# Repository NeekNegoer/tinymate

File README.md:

# TinyMate ♟️

**Eight Pin Gambit** — a smart chessboard that sees your pieces, powered by a single 8-pin ATtiny412.

> 🇧🇷 Um tabuleiro de xadrez inteligente que detecta as peças e joga online pelo Lichess, controlado por um microcontrolador de apenas 8 pinos.

Built for the [Hack Club 8-Pin Grant](https://8-pin-grant.hackclub.com/).

## How it works

```
[Phone/PC] ⇄ UART ⇄ [ATtiny412] ⇄ I2C ⇄ [MCP23017] ⇄ [8×8 reed switch matrix]
```

- Every piece has a small magnet in its base; every square has a reed switch (+ a 1N4148 diode to prevent ghosting).
- The ATtiny412 scans the 8×8 matrix through an MCP23017 I/O expander (8 rows out, 8 columns in) and reports occupied squares over UART.
- Software on the phone/PC compares board states to infer moves (from the starting position, including captures, castling and promotion) and plays them through the [Lichess Board API](https://lichess.org/api#tag/Board).

## ATtiny412 pinout

| Pin | Name | Use |
|---|---|---|
| 1 | VDD | 5 V |
| 2 | PA6 | UART TX |
| 3 | PA7 | UART RX |
| 4 | PA1 | I2C SDA |
| 5 | PA2 | I2C SCL |
| 6 | PA0 | UPDI (programming) |
| 7 | PA3 | Status LED |
| 8 | GND | Ground |

## Controller board parts (draft)

| Ref | Part | Notes |
|---|---|---|
| U1 | ATtiny412 (SOIC-8) | the brain |
| U2 | MCP23017 (SOIC-28) | A0–A2 → GND (addr 0x20), RESET → VCC |
| R1, R2 | 4.7 kΩ | I2C pull-ups |
| R3 + LED1 | 1 kΩ + LED | status |
| R4 | 10 kΩ | MCP23017 RESET pull-up |
| C1, C2 | 100 nF | decoupling, one per IC |
| C3 | 10 µF | bulk |
| J1 | 1×4 header | 5V / GND / TX / RX (also powers the board) |
| J2 | 1×3 header | UPDI: 5V / UPDI / GND |
| J3 | 2×8 header | matrix rows + columns |

## Status

- [x] Architecture, pinout and parts list
- [ ] Schematic (KiCad)
- [ ] PCB layout (KiCad, 2 layers)
- [ ] BOM with part numbers + cost check
- [ ] Submit to 8-Pin Grant
- [ ] Assemble, firmware, demo video
- [ ] Lichess bridge app

Progress log: [journal.md](journal.md)

## Author

Pietro Justino — [@NeekNegoer](https://github.com/NeekNegoer)

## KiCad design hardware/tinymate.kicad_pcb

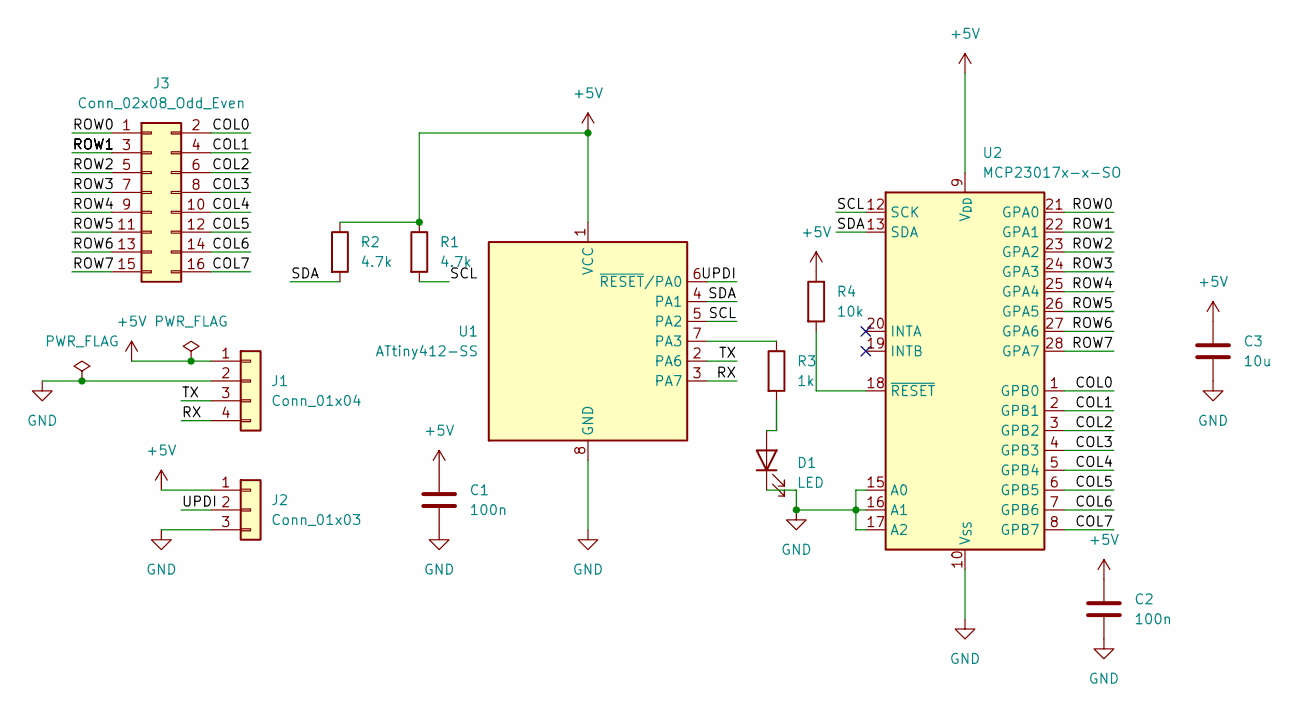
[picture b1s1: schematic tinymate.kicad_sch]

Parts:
C1, C2: 100n; C_0805_2012Metric_Pad1.18x1.45mm_HandSolder; MPN CL21B104KBCNNNC
C3: 10u; C_0805_2012Metric_Pad1.18x1.45mm_HandSolder; MPN CL21B106KOQNNNE
D1: LED; LED_0805_2012Metric_Pad1.15x1.40mm_HandSolder; MPN LTST-C171KRKT
J1: Conn_01x04; PinHeader_1x04_P2.54mm_Vertical; MPN PRPC040SAAN-RC
J2: Conn_01x03; PinHeader_1x03_P2.54mm_Vertical; MPN PRPC040SAAN-RC
J3: Conn_02x08_Odd_Even; PinHeader_2x08_P2.54mm_Vertical; MPN PRPC040SAAN-RC
R1, R2: 4.7k; R_0805_2012Metric_Pad1.20x1.40mm_HandSolder; MPN RC0805FR-074K7L
R3: 1k; R_0805_2012Metric_Pad1.20x1.40mm_HandSolder; MPN RC0805FR-071KL
R4: 10k; R_0805_2012Metric_Pad1.20x1.40mm_HandSolder; MPN RC0805FR-0710KL
U1: ATtiny412-SS; SOIC-8_3.9x4.9mm_P1.27mm; MPN ATTINY412-SSN
U2: MCP23017x-x-SO; SOIC-28W_7.5x17.9mm_P1.27mm; MPN MCP23017-E/SO

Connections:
+5V: C1.1, C2.1, C3.1, J1.1, J2.1, R1.1, R2.1, R4.1, U1.1 (VCC), U2.9 (V_{DD})
/COL0: J3.2, U2.1 (GPB0)
/COL1: J3.4, U2.2 (GPB1)
/COL2: J3.6, U2.3 (GPB2)
/COL3: J3.8, U2.4 (GPB3)
/COL4: J3.10, U2.5 (GPB4)
/COL5: J3.12, U2.6 (GPB5)
/COL6: J3.14, U2.7 (GPB6)
/COL7: J3.16, U2.8 (GPB7)
/ROW0: J3.1, U2.21 (GPA0)
/ROW1: J3.3, U2.22 (GPA1)
/ROW2: J3.5, U2.23 (GPA2)
/ROW3: J3.7, U2.24 (GPA3)
/ROW4: J3.9, U2.25 (GPA4)
/ROW5: J3.11, U2.26 (GPA5)
/ROW6: J3.13, U2.27 (GPA6)
/ROW7: J3.15, U2.28 (GPA7)
/RX: J1.4, U1.3 (PA7)
/SCL: R1.2, U1.5 (PA2), U2.12 (SCK)
/SDA: R2.2, U1.4 (PA1), U2.13 (SDA)
/TX: J1.3, U1.2 (PA6)
/UPDI: J2.2, U1.6 (~RESET/PA0)
GND: C1.2, C2.2, C3.2, D1.1 (K), J1.2, J2.3, U1.8 (GND), U2.10 (V_{SS}), U2.15 (A0), U2.16 (A1), U2.17 (A2)
unnamed: D1.2 (A), R3.2
unnamed: R3.1, U1.7 (PA3)
unnamed: R4.2, U2.18 (~RESET)

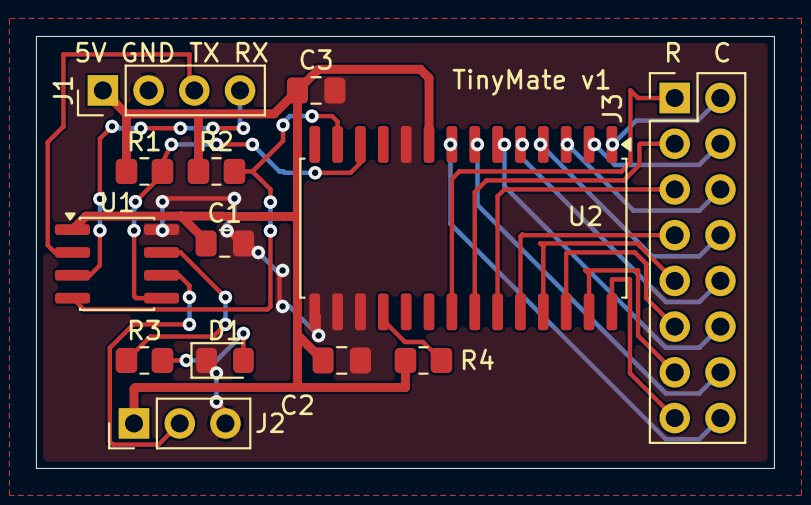
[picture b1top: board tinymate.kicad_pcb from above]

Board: 2 copper layers, 41.0 x 24.0 mm, 13 parts (0 on the bottom side), 26 nets.

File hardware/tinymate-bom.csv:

Reference,Qty on board,Value,Footprint,Manufacturer,Part Number,DigiKey Part Number,Order Qty,Unit Price (USD),Extended Price (USD)
U1,1,ATtiny412-SS,Package_SO:SOIC-8_3.9x4.9mm_P1.27mm,Microchip Technology,ATTINY412-SSN,ATTINY412-SSN-ND,2,0.56,1.12
U2,1,MCP23017,Package_SO:SOIC-28W_7.5x17.9mm_P1.27mm,Microchip Technology,MCP23017-E/SO,MCP23017-E/SO-ND,1,1.62,1.62
"R1,R2",2,4.7k,Resistor_SMD:R_0805_2012Metric_Pad1.20x1.40mm_HandSolder,YAGEO,RC0805FR-074K7L,311-4.70KCRCT-ND,10,0.038,0.38
R3,1,1k,Resistor_SMD:R_0805_2012Metric_Pad1.20x1.40mm_HandSolder,YAGEO,RC0805FR-071KL,311-1.00KCRCT-ND,10,0.038,0.38
R4,1,10k,Resistor_SMD:R_0805_2012Metric_Pad1.20x1.40mm_HandSolder,YAGEO,RC0805FR-0710KL,311-10.0KCRCT-ND,10,0.038,0.38
"C1,C2",2,100n,Capacitor_SMD:C_0805_2012Metric_Pad1.18x1.45mm_HandSolder,Samsung Electro-Mechanics,CL21B104KBCNNNC,1276-1003-1-ND,10,0.045,0.45
C3,1,10u,Capacitor_SMD:C_0805_2012Metric_Pad1.18x1.45mm_HandSolder,Samsung Electro-Mechanics,CL21B106KOQNNNE,1276-2872-1-ND,5,0.27,1.35
D1,1,LED red,LED_SMD:LED_0805_2012Metric_Pad1.15x1.40mm_HandSolder,Lite-On Inc.,LTST-C171KRKT,160-1427-1-ND,5,0.16,0.80
"J1,J2,J3",3,"Pin headers 1x4, 1x3, 2x8 (cut from 40-pin strips)",Connector_PinHeader_2.54mm:PinHeader_1x04/1x03/2x08_P2.54mm_Vertical,Sullins Connector Solutions,PRPC040SAAN-RC,S1011EC-40-ND,2,1.23,2.46
,,,,,,,,TOTAL,8.94
